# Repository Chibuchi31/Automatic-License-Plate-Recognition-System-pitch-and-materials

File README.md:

\# **Automatic License Plate Recognition (ALPR) System**

**IoT-based license plate recognition system using computer vision, OCR, and ESP32-CAM.**

\## Overview

This project implements an ALPR system designed for vehicle identification and

crime investigation use cases. It combines an ESP32-based hardware design with

a Python simulation pipeline that detects and reads license plates from images

using OpenCV and Tesseract OCR.

\## Hardware Design

Designed in KiCad. Key components:

\- \*\*ESP32-WROOM-32\*\* — main microcontroller

\- \*\*AMS1117-3.3\*\* — 3.3V voltage regulator

\- \*\*ER\_OLEDM0.91 (I2C)\*\* — 0.91" OLED display

\- \*\*FTDI Header\*\* — for serial programming

\- \*\*Resistors:\*\* R1 (10kΩ), R2 (4.7kΩ), R3 (4.7kΩ)

\- \*\*Capacitors:\*\* C1, C2 (10µF)

Schematic and PCB files are included in this repository.

\## Software Simulation

The Python simulation runs the full ALPR pipeline on a local image:

1\. Load image from disk

2\. Preprocess (grayscale → Gaussian blur → adaptive threshold → Canny edges)

3\. Detect license plate contour by aspect ratio and area filtering

4\. Extract plate region

5\. Run Tesseract OCR on the extracted region

6\. Display annotated result

\### Requirements

pip install opencv-python pytesseract numpy

\[Tesseract OCR](https://github.com/tesseract-ocr/tesseract) must be installed separately.

\### Run

python alpr\_esp32\_system.py

Set `IMAGE\_PATH` in the script to your test image filename before running.

\## Repository Contents

| File | Description |

|------|-------------|

| `ALPR\_ESP32\_System.kicad\_sch` | KiCad schematic |

| `ALPR\_ESP32\_System.kicad\_pcb` | PCB layout |

| `ALPR\_ESP32\_System.pdf` | Schematic export (PDF) |

| `ALPR\_ESP32\_System.csv` | Bill of materials |

| `ALPR\_ESP32\_System code note.txt` | Python simulation code and notes |

| `report ALPR\_ESP32.txt` | KiCad ERC report |

\## Status

Hardware design complete. Python simulation pipeline functional.

ESP32-CAM firmware integration in progress.

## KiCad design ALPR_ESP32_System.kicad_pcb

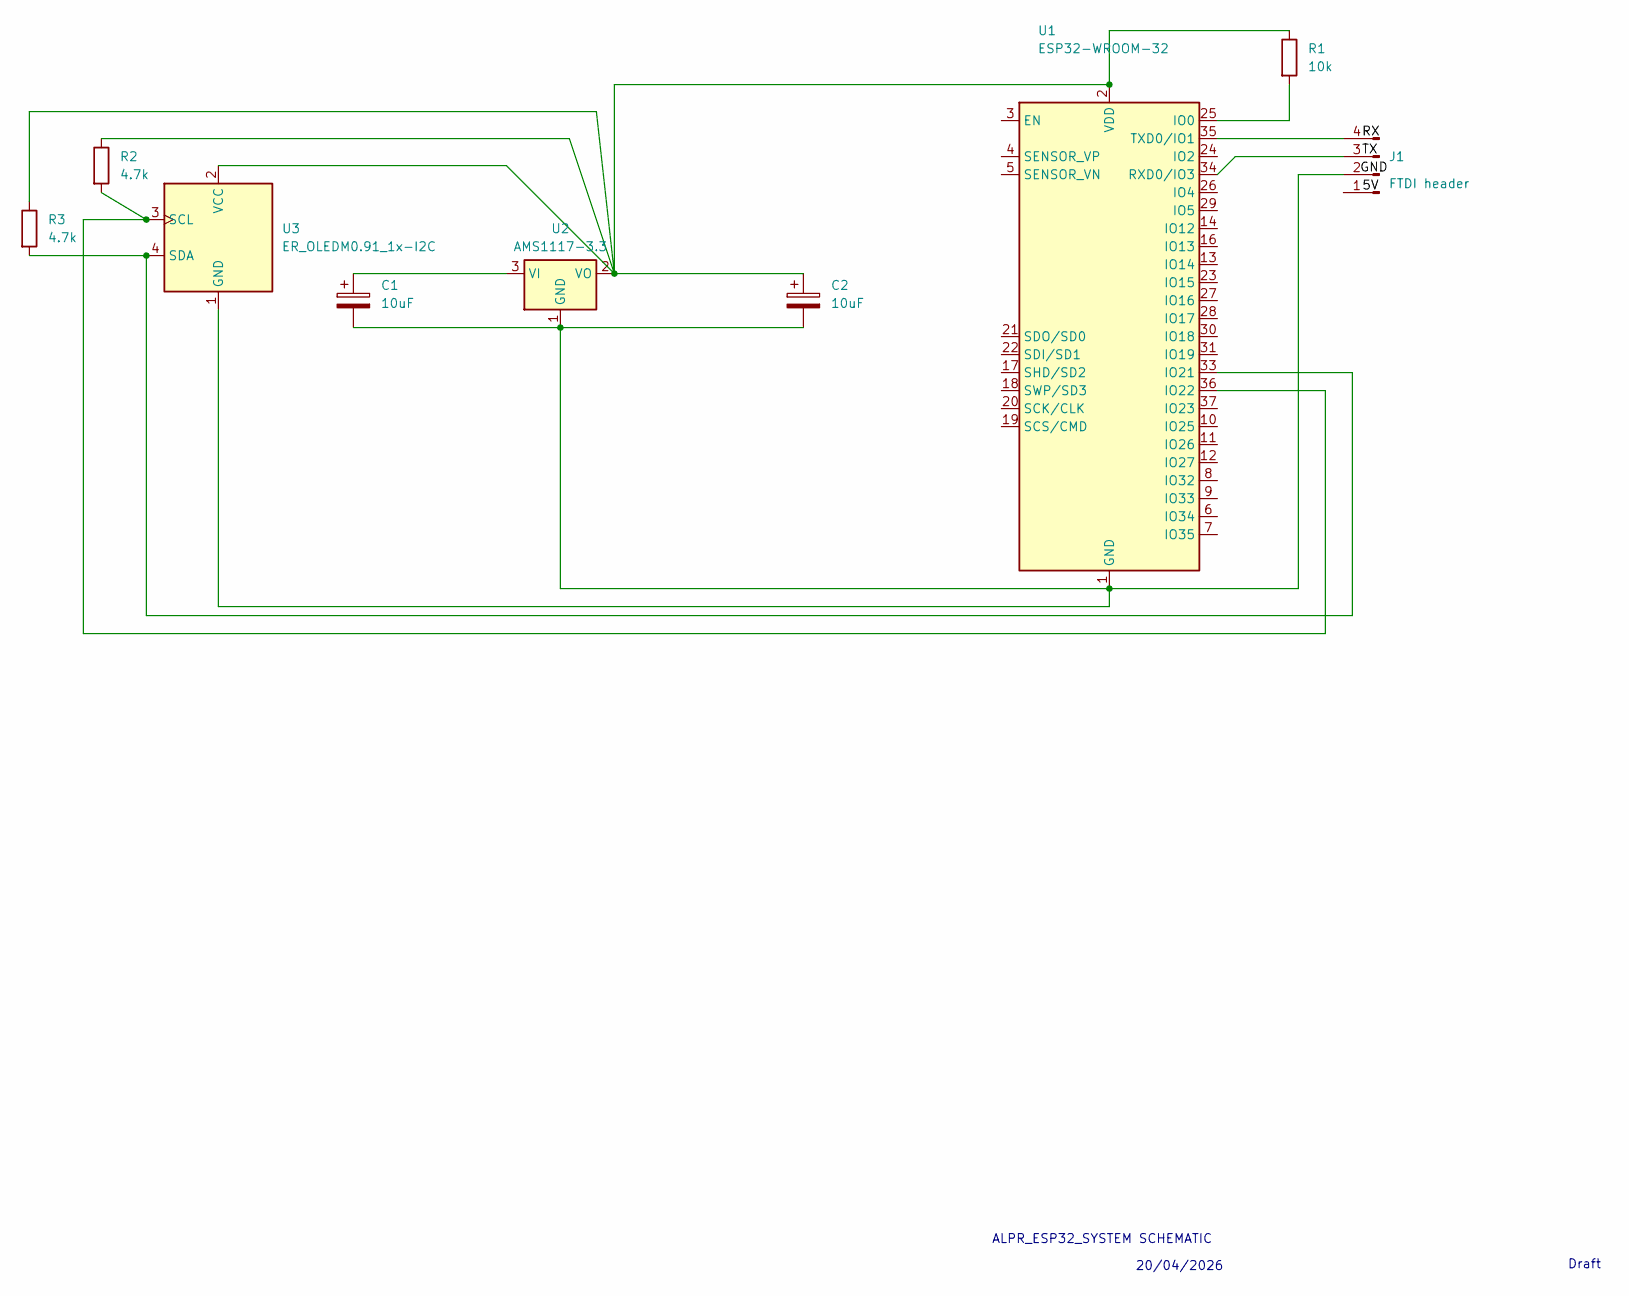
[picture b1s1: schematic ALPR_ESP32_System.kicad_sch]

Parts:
C1, C2: 10uF; CP_Radial_D5.0mm_P2.00mm
J1: FTDI header; PinHeader_1x04_P1.00mm_Horizontal
R1: 10k; R_0805_2012Metric
R2, R3: 4.7k; R_0805_2012Metric
U1: ESP32-WROOM-32
U2: AMS1117-3.3; SOT-223-3_TabPin2
U3: ER_OLEDM0.91_1x-I2C; PinHeader_1x04_P2.54mm_Vertical

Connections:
unnamed: C1.2, C2.2, J1.2, U1.1 (GND), U1.15 (GND), U1.38 (GND), U1.39 (GND), U2.1 (GND), U3.1 (GND)
unnamed: J1.3, U1.34 (RXD0/IO3)
unnamed: J1.4, U1.35 (TXD0/IO1)
unnamed: R1.2, U1.25 (IO0)
unnamed: R3.2, U1.33 (IO21), U3.4 (SDA)
unnamed: R2.2, U1.36 (IO22), U3.3 (SCL)
unnamed: C2.1, R1.1, R2.1, R3.1, U1.2 (VDD), U2.2 (VO), U3.2 (VCC)
unnamed: C1.1, U2.3 (VI)

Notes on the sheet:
ALPR_ESP32_SYSTEM SCHEMATIC
20/04/2026
Draft

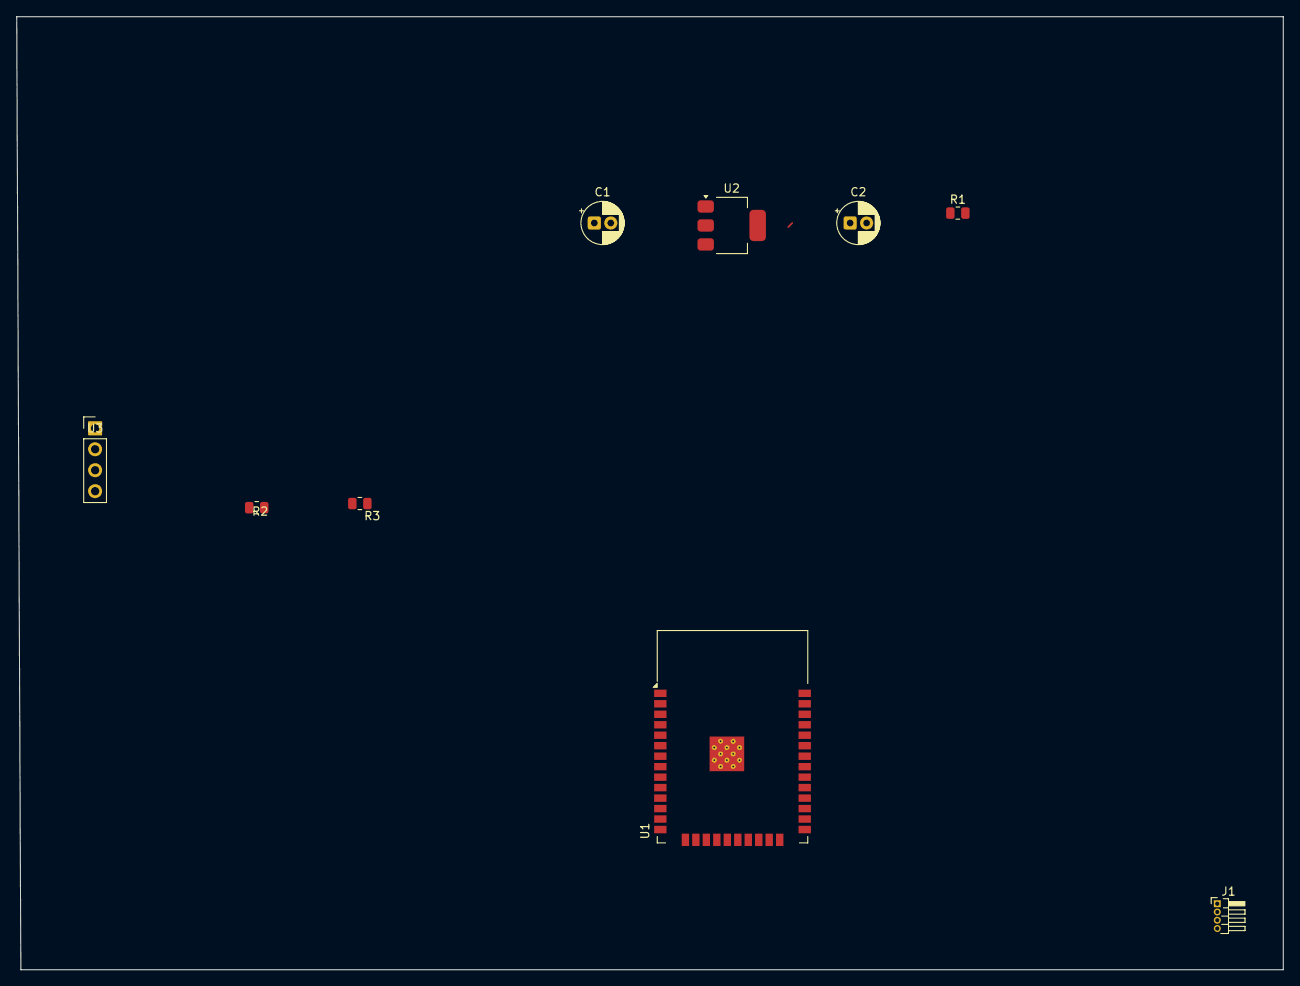
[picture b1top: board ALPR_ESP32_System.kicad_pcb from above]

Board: 2 copper layers, 153.5 x 115.5 mm, 9 parts (0 on the bottom side), 8 nets.
